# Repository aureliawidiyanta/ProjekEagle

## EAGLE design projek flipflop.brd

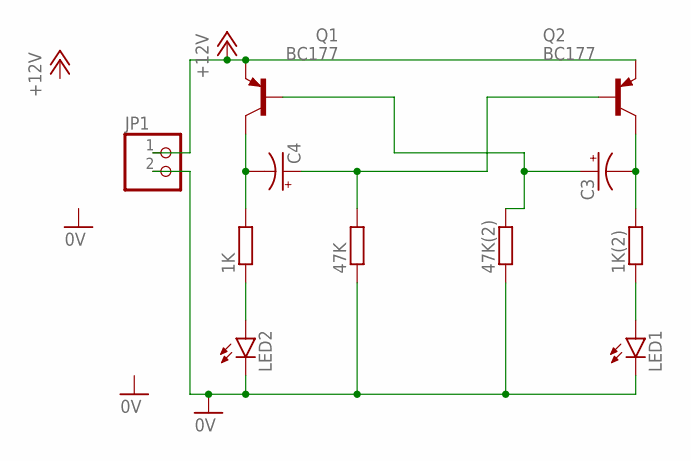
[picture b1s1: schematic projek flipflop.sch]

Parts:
1K, 1K(2), 47K, 47K(2): R-EU_0207/15; 0207/15
C3, C4: CPOL-USE2.5-5; E2,5-5
JP1: PINHD-1X2; 1X02
LED1, LED2: LED5MM
Q1, Q2: BC177; TO18

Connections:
0V: 47K.1, 47K(2).1, JP1.2, LED1.K (C), LED2.K (C)
+12V: JP1.1, Q1.1 (E), Q2.1 (E)
unnamed: 1K.2, C4.-, Q1.3 (C)
unnamed: 47K(2).2, C3.+, Q1.2 (B)
unnamed: 47K.2, C4.+, Q2.2 (B)
unnamed: 1K(2).2, C3.-, Q2.3 (C)
unnamed: 1K.1, LED2.A
unnamed: 1K(2).1, LED1.A

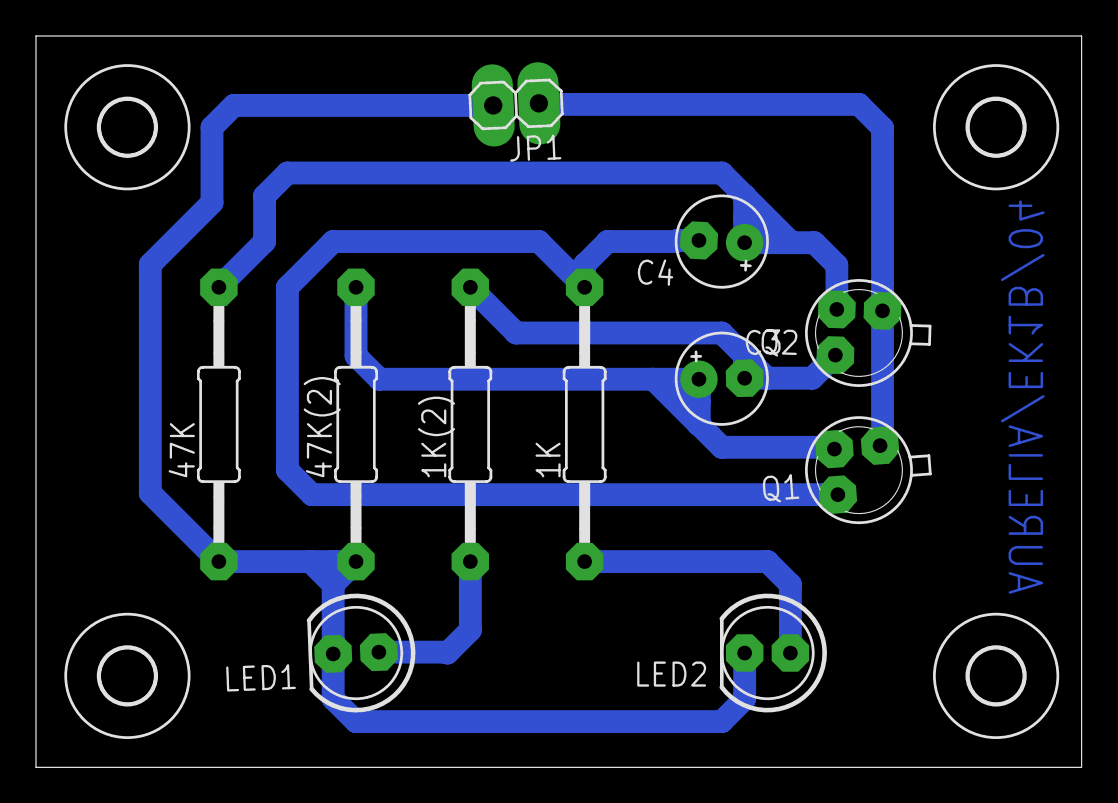
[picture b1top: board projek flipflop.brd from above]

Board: 2 copper layers, 58.1 x 40.6 mm, 15 parts (0 on the bottom side), 8 nets.

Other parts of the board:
U$1, U$2, U$3, U$4: 3,0

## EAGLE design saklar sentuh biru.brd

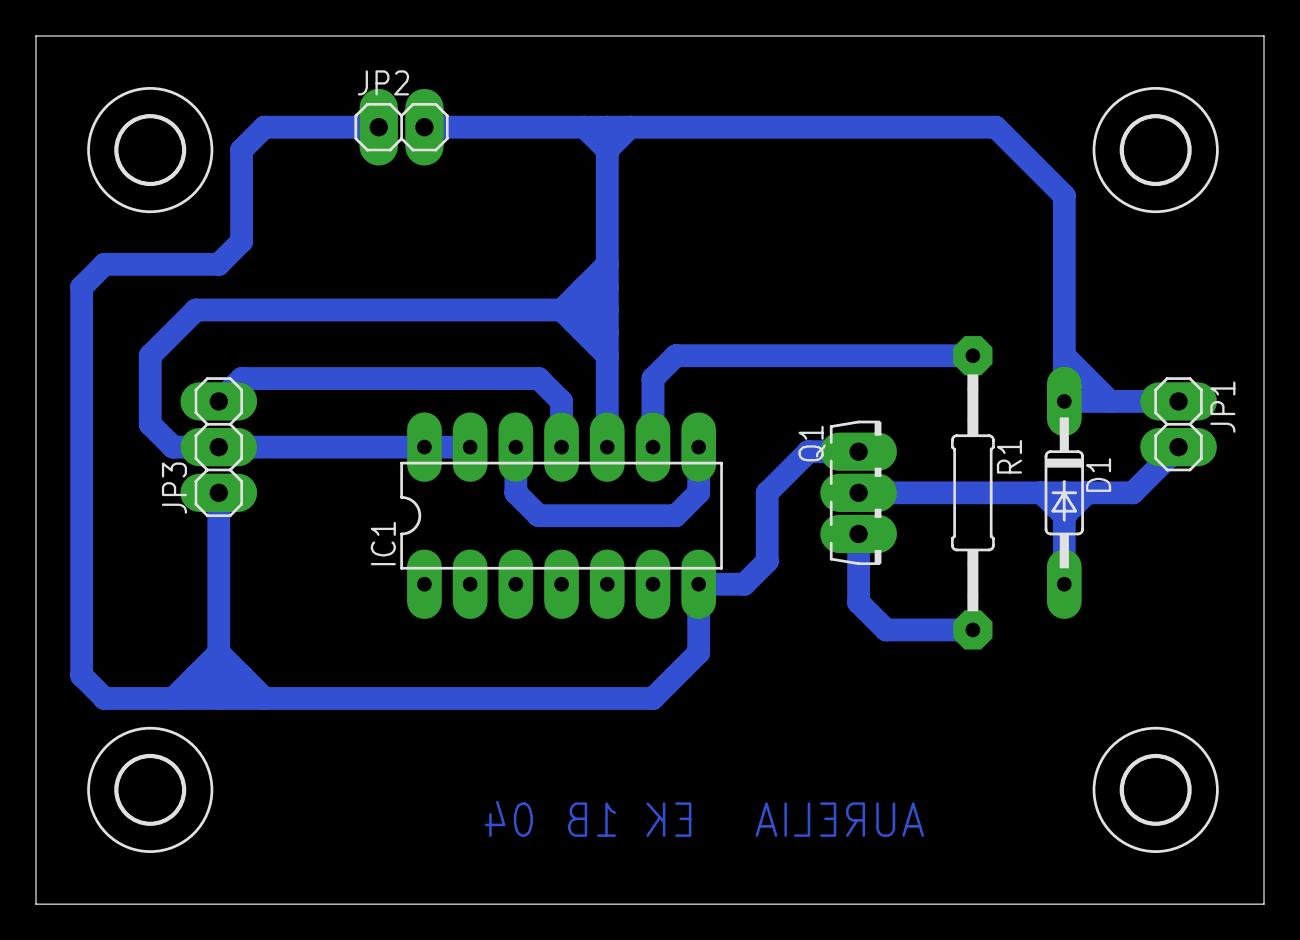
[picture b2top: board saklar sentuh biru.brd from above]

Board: 2 copper layers, 68.2 x 48.2 mm, 11 parts (0 on the bottom side), 7 nets.

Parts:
D1: 1N4148DO35-10; DO35-10
H1, H2, H3, H4: MOUNT-HOLE3.6; 3,6
IC1: 74AC74N; DIL14
JP1, JP2: 1X02
JP3: 1X03
Q1: BD139; TO126AV
R1: 0207/15

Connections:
GND: IC1.7, JP2.1, JP3.1, Q1.E
unnamed: IC1.9, R1.1
unnamed: Q1.B, R1.2
unnamed: D1.A, JP1.2, Q1.C
unnamed: IC1.11, JP3.3
unnamed: IC1.8, IC1.12
VCC: D1.C, IC1.10, IC1.13, IC1.14, JP1.1, JP2.2, JP3.2
